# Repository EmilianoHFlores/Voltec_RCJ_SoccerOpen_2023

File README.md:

# Voltec_RCJ_SoccerOpen_2023
 Source programs. libraries, electronic schematicsm designs and CAD files from the 2023 Voltec Robocup team, participating in TMR 2023 Soccer Open category.

## Arduino Programs
 All arduino libraries and programs are created for running on an ATMEGA-2560 chip. For pin assignments, refer to the pcb schematics and design.

## PCBs
 PCB design files were created on Autodesk Eagle 9.6.2. Library requirements and references are included on folder.

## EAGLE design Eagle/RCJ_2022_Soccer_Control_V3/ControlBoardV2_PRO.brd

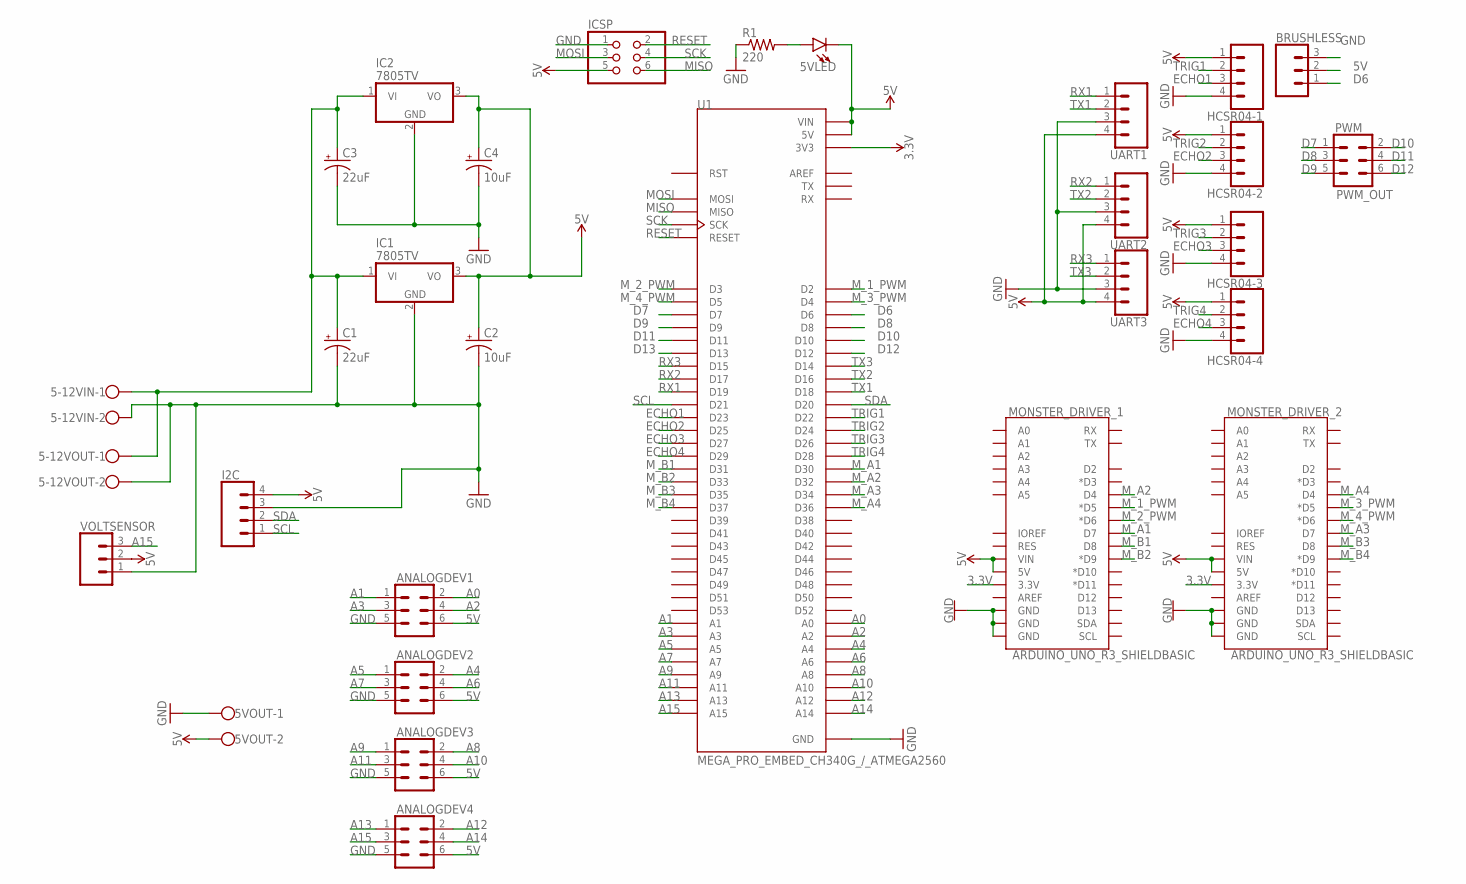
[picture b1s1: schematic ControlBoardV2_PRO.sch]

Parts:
5-12VIN, 5-12VOUT, 5VOUT: W237-102
5VLED: LED5MM; LED_5MM
ANALOGDEV1, ANALOGDEV2, ANALOGDEV3, ANALOGDEV4: CONN_03X2NO_SILK; 2X3-NS
BRUSHLESS: CONN_03; 1X03
C1, C3: 22uF; E2,5-5
C2, C4: 10uF; E2,5-5
HCSR04-1, HCSR04-2, HCSR04-3, HCSR04-4: CONN_04; 1X04
I2C: CONN_04; 1X04
IC1, IC2: 7805TV; TO220V
ICSP: PINHD-2X3; 2X03
MONSTER_DRIVER_1, MONSTER_DRIVER_2: ARDUINO_UNO_R3_SHIELDBASIC; UNO_R3_SHIELD
PWM: PWM_OUT; 2X3
R1: 220; 0204/7
U1: MEGA_PRO_EMBED_CH340G_/_ATMEGA2560; MODULE_MEGA_PRO_EMBED_CH340G_/_ATMEGA2560
UART1, UART2, UART3: CONN_04; 1X04
VOLTSENSOR: CONN_03; 1X03

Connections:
3.3V: MONSTER_DRIVER_1.3.3V, MONSTER_DRIVER_2.3.3V, U1.3V3_1 (3V3), U1.3V3_2 (3V3)
5V: 5VLED.K (C), 5VOUT.2, ANALOGDEV1.6, ANALOGDEV2.6, ANALOGDEV3.6, ANALOGDEV4.6, BRUSHLESS.2, C2.+, C4.+, HCSR04-1.1, HCSR04-2.1, HCSR04-3.1, HCSR04-4.1, I2C.4, IC1.3 (VO), IC2.3 (VO), ICSP.5, MONSTER_DRIVER_1.5V, MONSTER_DRIVER_1.VIN, MONSTER_DRIVER_2.5V, MONSTER_DRIVER_2.VIN, U1.5V_1 (5V), U1.5V_2 (5V), U1.5V_3 (5V), U1.VIN_1 (VIN), U1.VIN_2 (VIN), UART1.4, UART2.4, UART3.4, VOLTSENSOR.2
A0: ANALOGDEV1.2, U1.A0
A1: ANALOGDEV1.1, U1.A1
A2: ANALOGDEV1.4, U1.A2
A3: ANALOGDEV1.3, U1.A3
A4: ANALOGDEV2.2, U1.A4
A5: ANALOGDEV2.1, U1.A5
A6: ANALOGDEV2.4, U1.A6
A7: ANALOGDEV2.3, U1.A7
A8: ANALOGDEV3.2, U1.A8
A9: ANALOGDEV3.1, U1.A9
A10: ANALOGDEV3.4, U1.A10
A11: ANALOGDEV3.3, U1.A11
A12: ANALOGDEV4.2, U1.A12
A13: ANALOGDEV4.1, U1.A13
A14: ANALOGDEV4.4, U1.A14
A15: ANALOGDEV4.3, U1.A15, VOLTSENSOR.3
D6: BRUSHLESS.1, U1.D6
D7: PWM.1, U1.D7
D8: PWM.3, U1.D8
D9: PWM.5, U1.D9
D10: PWM.2, U1.D10
D11: PWM.4, U1.D11
D12: PWM.6, U1.D12
D13: U1.D13
ECHO1: HCSR04-1.3, U1.D23
ECHO2: HCSR04-2.3, U1.D25
ECHO3: HCSR04-3.3, U1.D27
ECHO4: HCSR04-4.3, U1.D29
GND: 5-12VIN.2, 5-12VOUT.2, 5VOUT.1, ANALOGDEV1.5, ANALOGDEV2.5, ANALOGDEV3.5, ANALOGDEV4.5, BRUSHLESS.3, C1.-, C2.-, C3.-, C4.-, HCSR04-1.4, HCSR04-2.4, HCSR04-3.4, HCSR04-4.4, I2C.3, IC1.2 (GND), IC2.2 (GND), ICSP.1, MONSTER_DRIVER_1.GND@0 (GND), MONSTER_DRIVER_1.GND@1 (GND), MONSTER_DRIVER_1.GND@2 (GND), MONSTER_DRIVER_2.GND@0 (GND), MONSTER_DRIVER_2.GND@1 (GND), MONSTER_DRIVER_2.GND@2 (GND), R1.1, U1.GND_1 (GND), U1.GND_2 (GND), U1.GND_3 (GND), UART1.3, UART2.3, UART3.3, VOLTSENSOR.1
MISO: ICSP.6, U1.MISO
MOSI: ICSP.3, U1.MOSI
M_1_PWM: MONSTER_DRIVER_1.D5 (*D5), U1.D2
M_2_PWM: MONSTER_DRIVER_1.D6 (*D6), U1.D3
M_3_PWM: MONSTER_DRIVER_2.D5 (*D5), U1.D4
M_4_PWM: MONSTER_DRIVER_2.D6 (*D6), U1.D5
M_A1: MONSTER_DRIVER_1.D7, U1.D30
M_A2: MONSTER_DRIVER_1.D4, U1.D32
M_A3: MONSTER_DRIVER_2.D7, U1.D34
M_A4: MONSTER_DRIVER_2.D4, U1.D36
M_B1: MONSTER_DRIVER_1.D8, U1.D31
M_B2: MONSTER_DRIVER_1.D9 (*D9), U1.D33
M_B3: MONSTER_DRIVER_2.D8, U1.D35
M_B4: MONSTER_DRIVER_2.D9 (*D9), U1.D37
unnamed: 5VLED.A, R1.2
unnamed: 5-12VIN.1, 5-12VOUT.1, C1.+, C3.+, IC1.1 (VI), IC2.1 (VI)
RESET: ICSP.2, U1.RESET
RX1: U1.D19, UART1.1
RX2: U1.D17, UART2.1
RX3: U1.D15, UART3.1
SCK: ICSP.4, U1.SCK
SCL: I2C.1, U1.D21
SDA: I2C.2, U1.D20
TRIG1: HCSR04-1.2, U1.D22
TRIG2: HCSR04-2.2, U1.D24
TRIG3: HCSR04-3.2, U1.D26
TRIG4: HCSR04-4.2, U1.D28
TX1: U1.D18, UART1.2
TX2: U1.D16, UART2.2
TX3: U1.D14, UART3.2

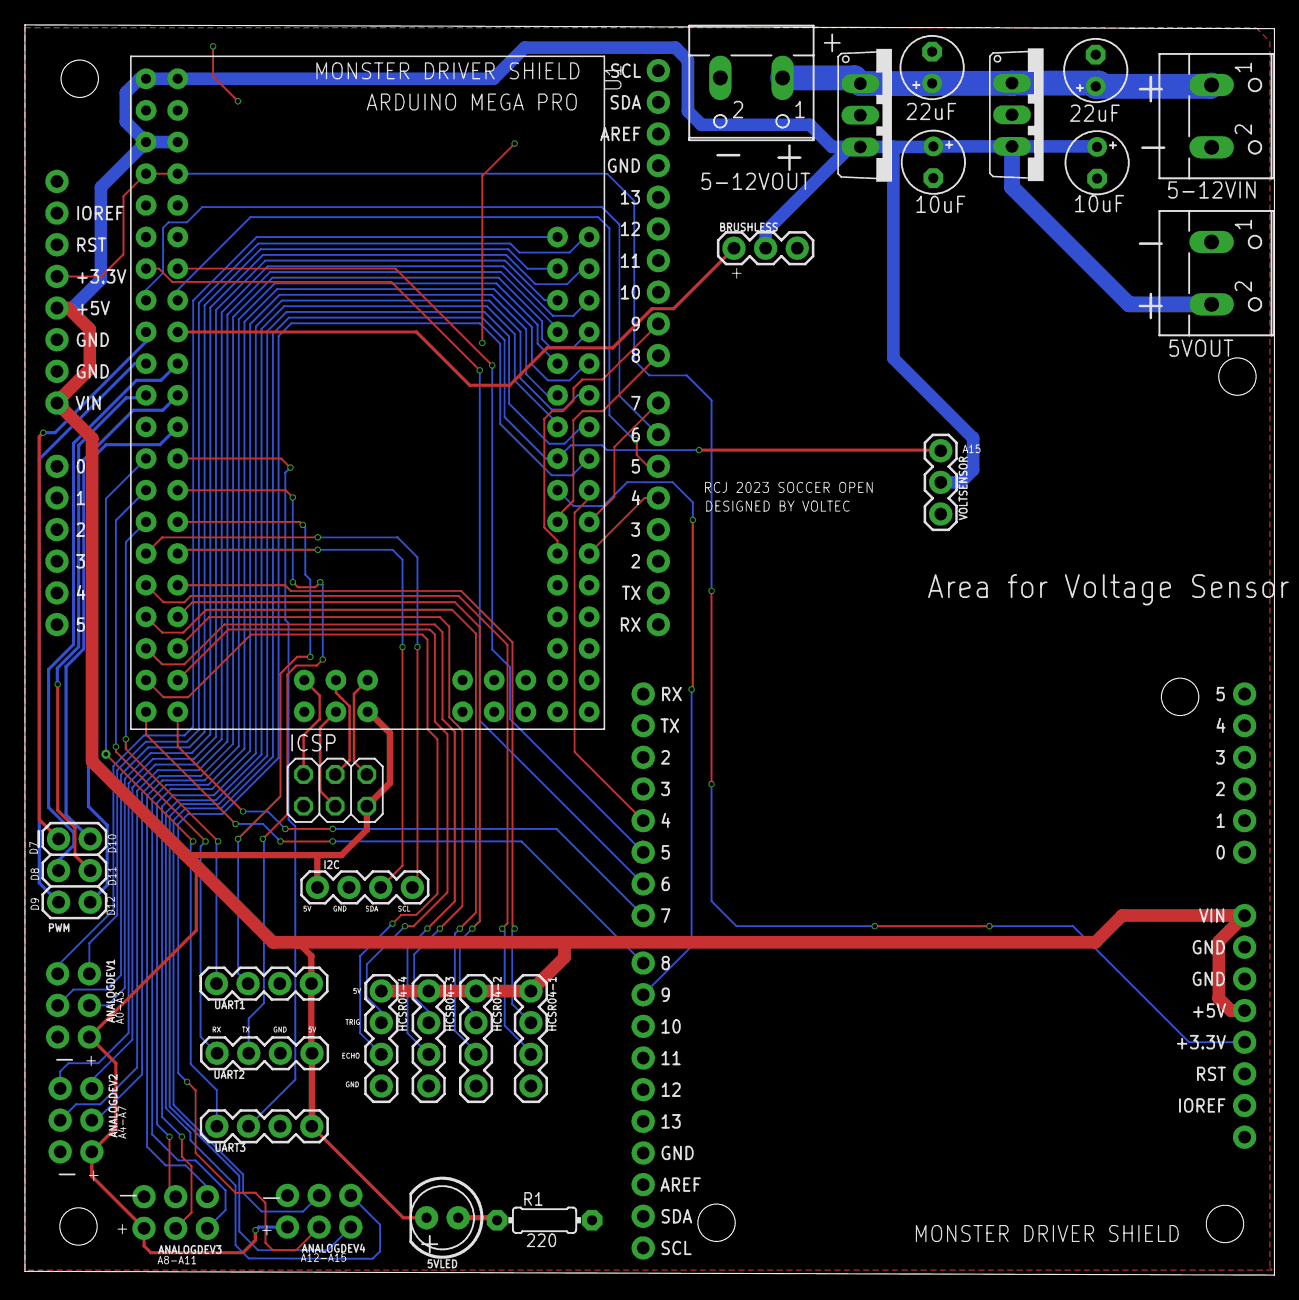
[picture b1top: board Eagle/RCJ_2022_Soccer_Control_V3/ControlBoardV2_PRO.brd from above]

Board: 2 copper layers, 100.3 x 100.3 mm, 30 parts (0 on the bottom side), 60 nets.

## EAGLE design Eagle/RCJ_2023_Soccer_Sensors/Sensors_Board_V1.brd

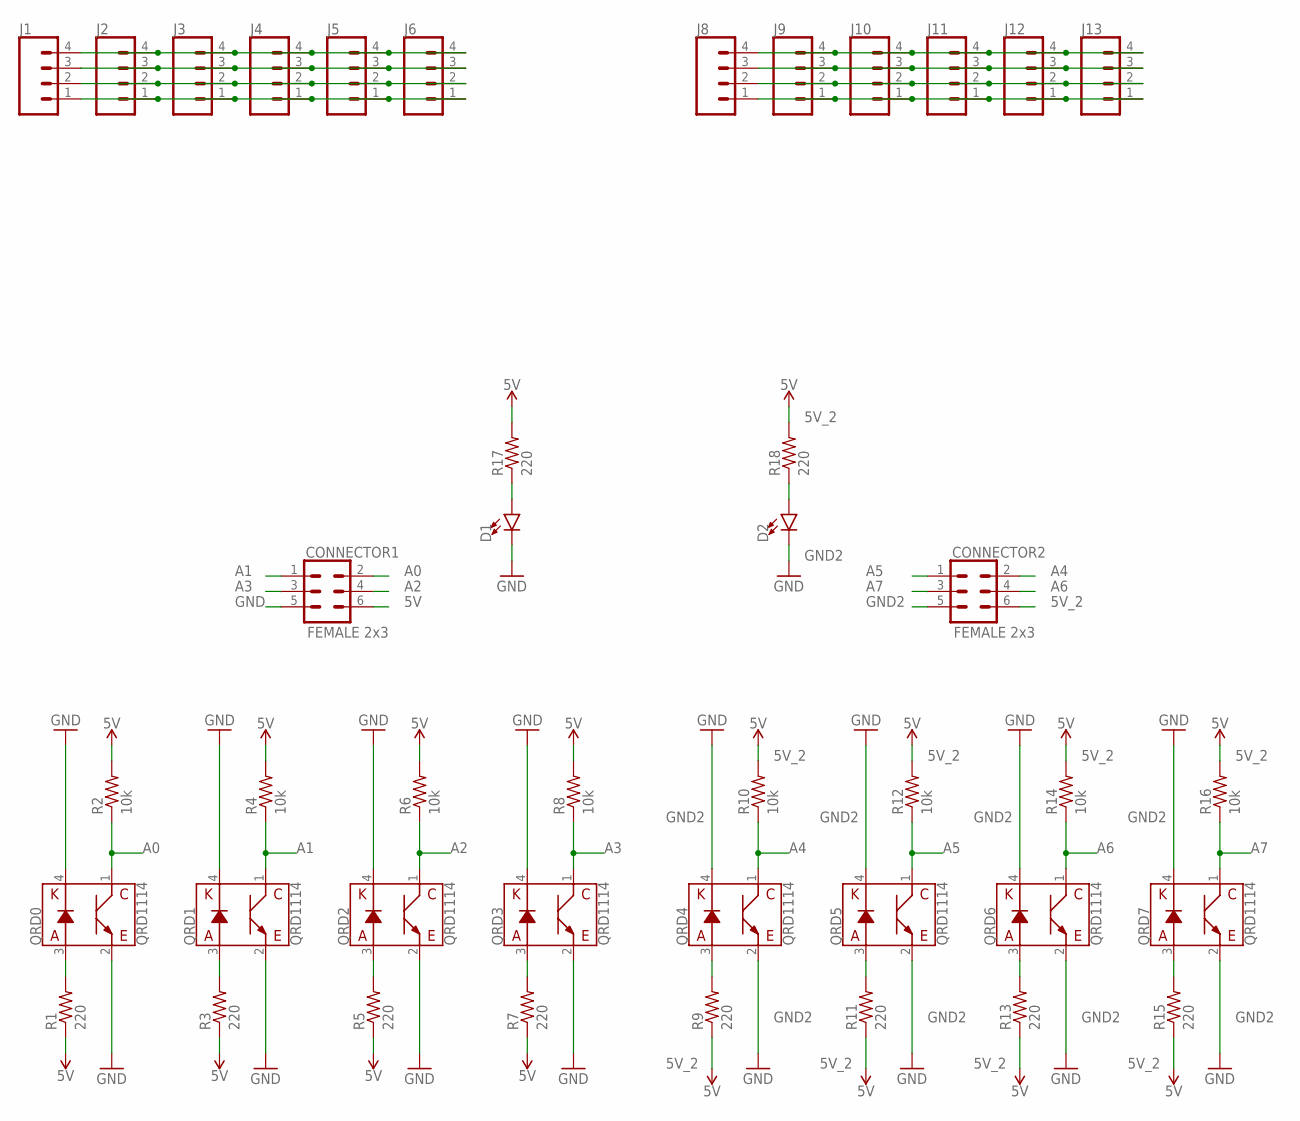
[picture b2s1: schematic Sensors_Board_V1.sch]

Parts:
CONNECTOR1, CONNECTOR2: FEMALE 2x3; 2X3
D1, D2: LED3MM; LED_3MM
J1, J2, J3, J4, J5, J6, J8, J9, J10, J11, J12, J13: CONN_04; 1X04
QRD0, QRD1, QRD2, QRD3, QRD4, QRD5, QRD6, QRD7: QRD1114
R1, R3, R5, R7, R9, R11, R13, R15, R17, R18: 220; 0204/7
R2, R4, R6, R8, R10, R12, R14, R16: 10k; 0204/7

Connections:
5V: CONNECTOR1.6, R1.1, R2.2, R3.1, R4.2, R5.1, R6.2, R7.1, R8.2, R17.2
5V_2: CONNECTOR2.6, R9.1, R10.2, R11.1, R12.2, R13.1, R14.2, R15.1, R16.2, R18.2
A0: CONNECTOR1.2, QRD0.1 (C), R2.1
A1: CONNECTOR1.1, QRD1.1 (C), R4.1
A2: CONNECTOR1.4, QRD2.1 (C), R6.1
A3: CONNECTOR1.3, QRD3.1 (C), R8.1
A4: CONNECTOR2.2, QRD4.1 (C), R10.1
A5: CONNECTOR2.1, QRD5.1 (C), R12.1
A6: CONNECTOR2.4, QRD6.1 (C), R14.1
A7: CONNECTOR2.3, QRD7.1 (C), R16.1
GND: CONNECTOR1.5, D1.K (C), QRD0.2 (E), QRD0.4 (K), QRD1.2 (E), QRD1.4 (K), QRD2.2 (E), QRD2.4 (K), QRD3.2 (E), QRD3.4 (K)
GND2: CONNECTOR2.5, D2.K (C), QRD4.2 (E), QRD4.4 (K), QRD5.2 (E), QRD5.4 (K), QRD6.2 (E), QRD6.4 (K), QRD7.2 (E), QRD7.4 (K)
unnamed: QRD0.3 (A), R1.2
unnamed: QRD1.3 (A), R3.2
unnamed: QRD2.3 (A), R5.2
unnamed: QRD3.3 (A), R7.2
unnamed: QRD4.3 (A), R9.2
unnamed: QRD5.3 (A), R11.2
unnamed: QRD6.3 (A), R13.2
unnamed: QRD7.3 (A), R15.2
unnamed: D1.A, R17.1
unnamed: D2.A, R18.1
unnamed: J1.4, J2.4, J3.4, J4.4, J5.4, J6.4
unnamed: J1.3, J2.3, J3.3, J4.3, J5.3, J6.3
unnamed: J1.2, J2.2, J3.2, J4.2, J5.2, J6.2
unnamed: J1.1, J2.1, J3.1, J4.1, J5.1, J6.1
unnamed: J8.4, J9.4, J10.4, J11.4, J12.4, J13.4
unnamed: J8.3, J9.3, J10.3, J11.3, J12.3, J13.3
unnamed: J8.2, J9.2, J10.2, J11.2, J12.2, J13.2
unnamed: J8.1, J9.1, J10.1, J11.1, J12.1, J13.1

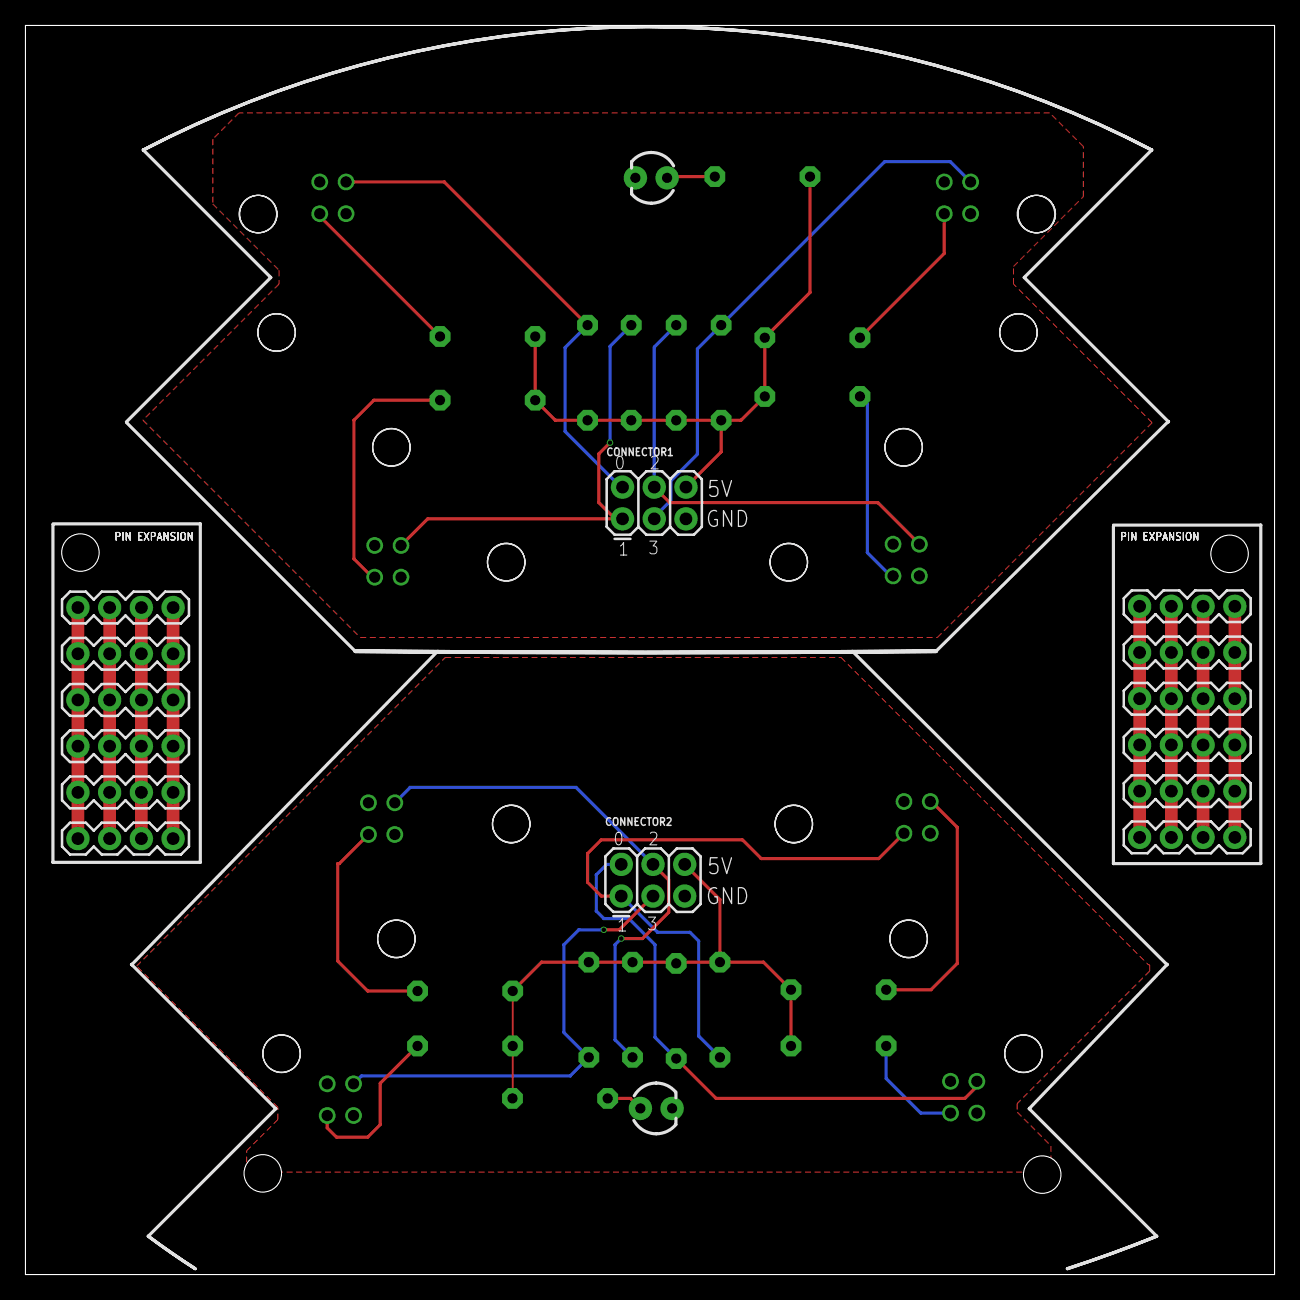
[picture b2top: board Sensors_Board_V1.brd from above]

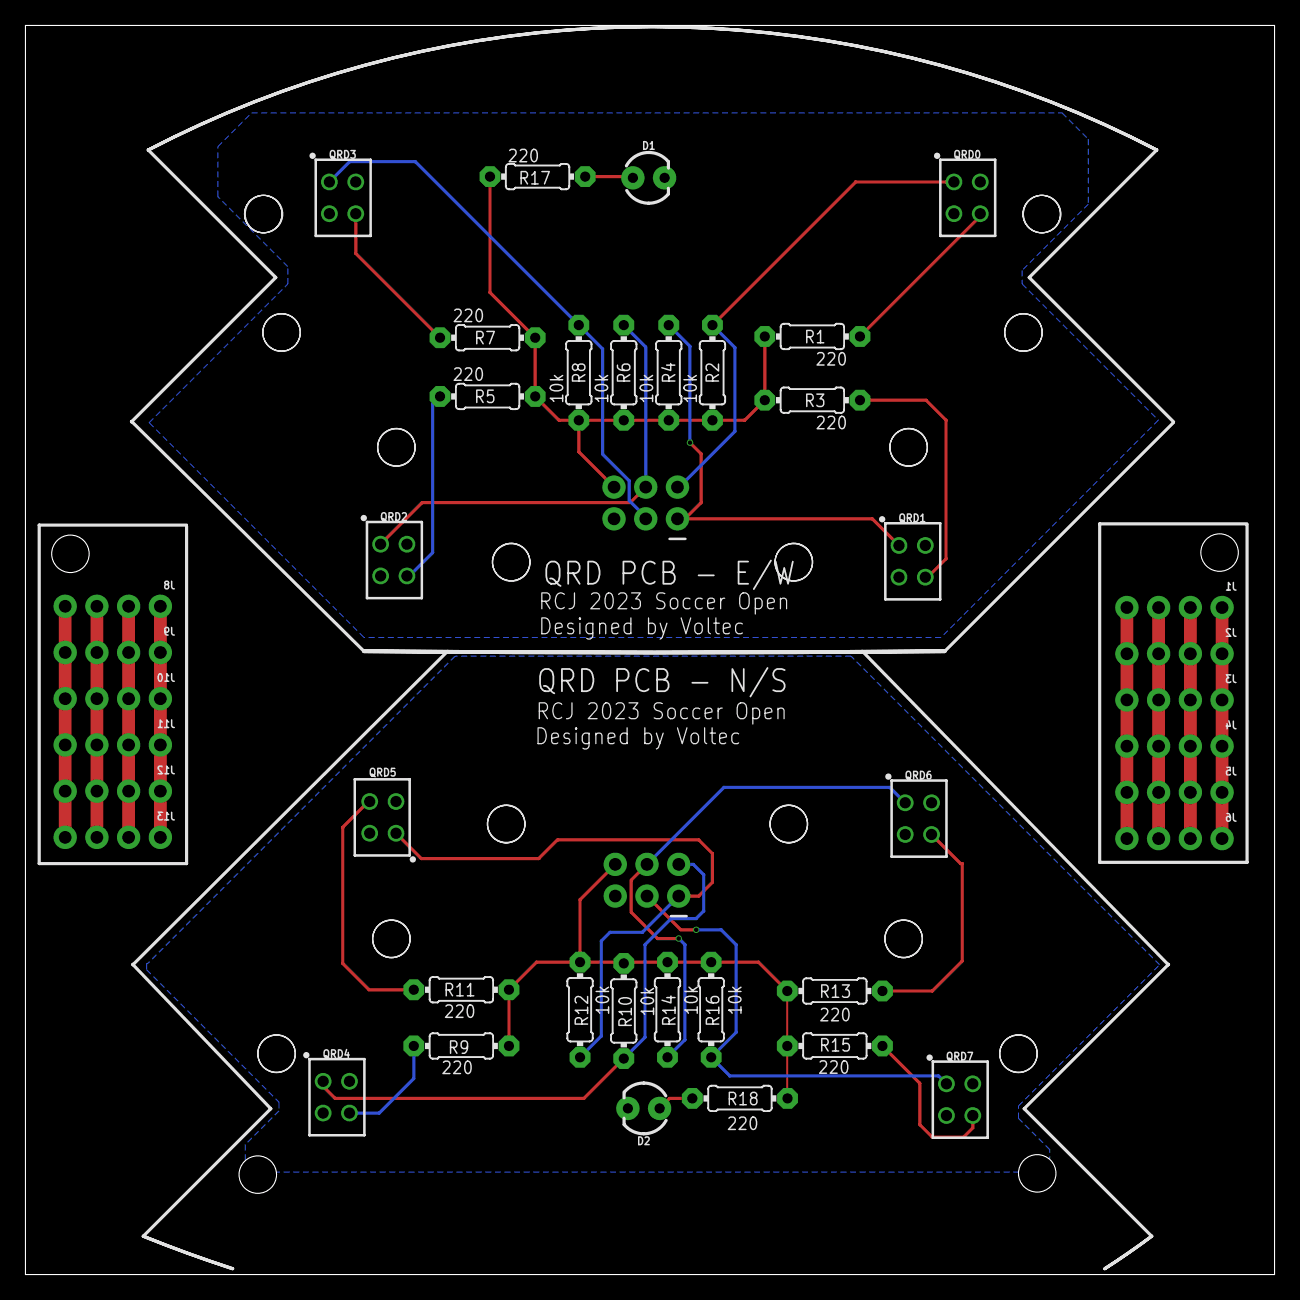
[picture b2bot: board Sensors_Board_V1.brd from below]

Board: 2 copper layers, 100.0 x 100.0 mm, 42 parts (28 on the bottom side), 30 nets.

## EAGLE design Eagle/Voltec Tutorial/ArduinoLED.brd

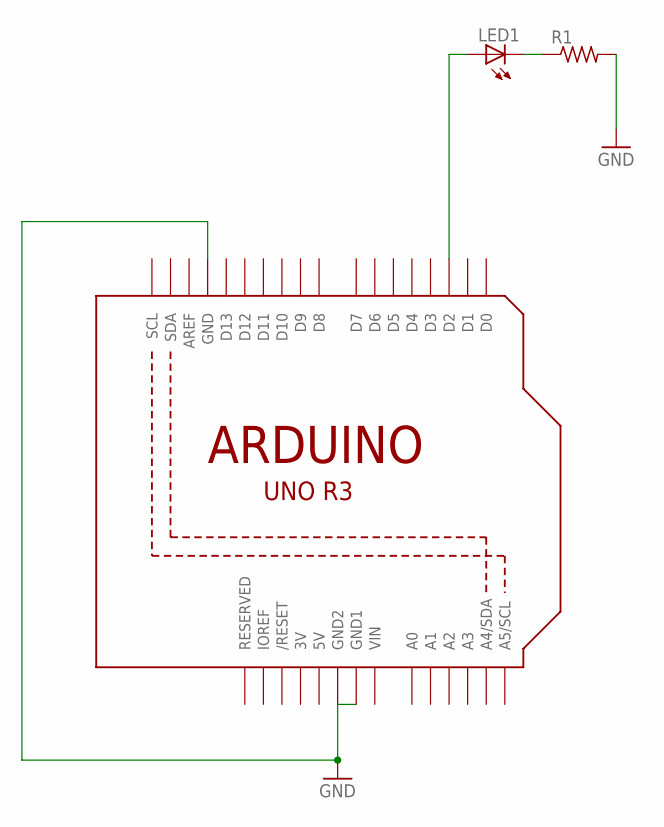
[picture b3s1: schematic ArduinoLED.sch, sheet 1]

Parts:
LED1: LED5MM
R1: R-US_0204/7; 0204/7
U1: ARDUINOR3-BPLACE

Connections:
3V: U1.3V
5V: U1.5V
GND: R1.2, U1.GND, U1.GND1, U1.GND2
unnamed: LED1.A, U1.D2
unnamed: LED1.K (C), R1.1
VIN: U1.VIN

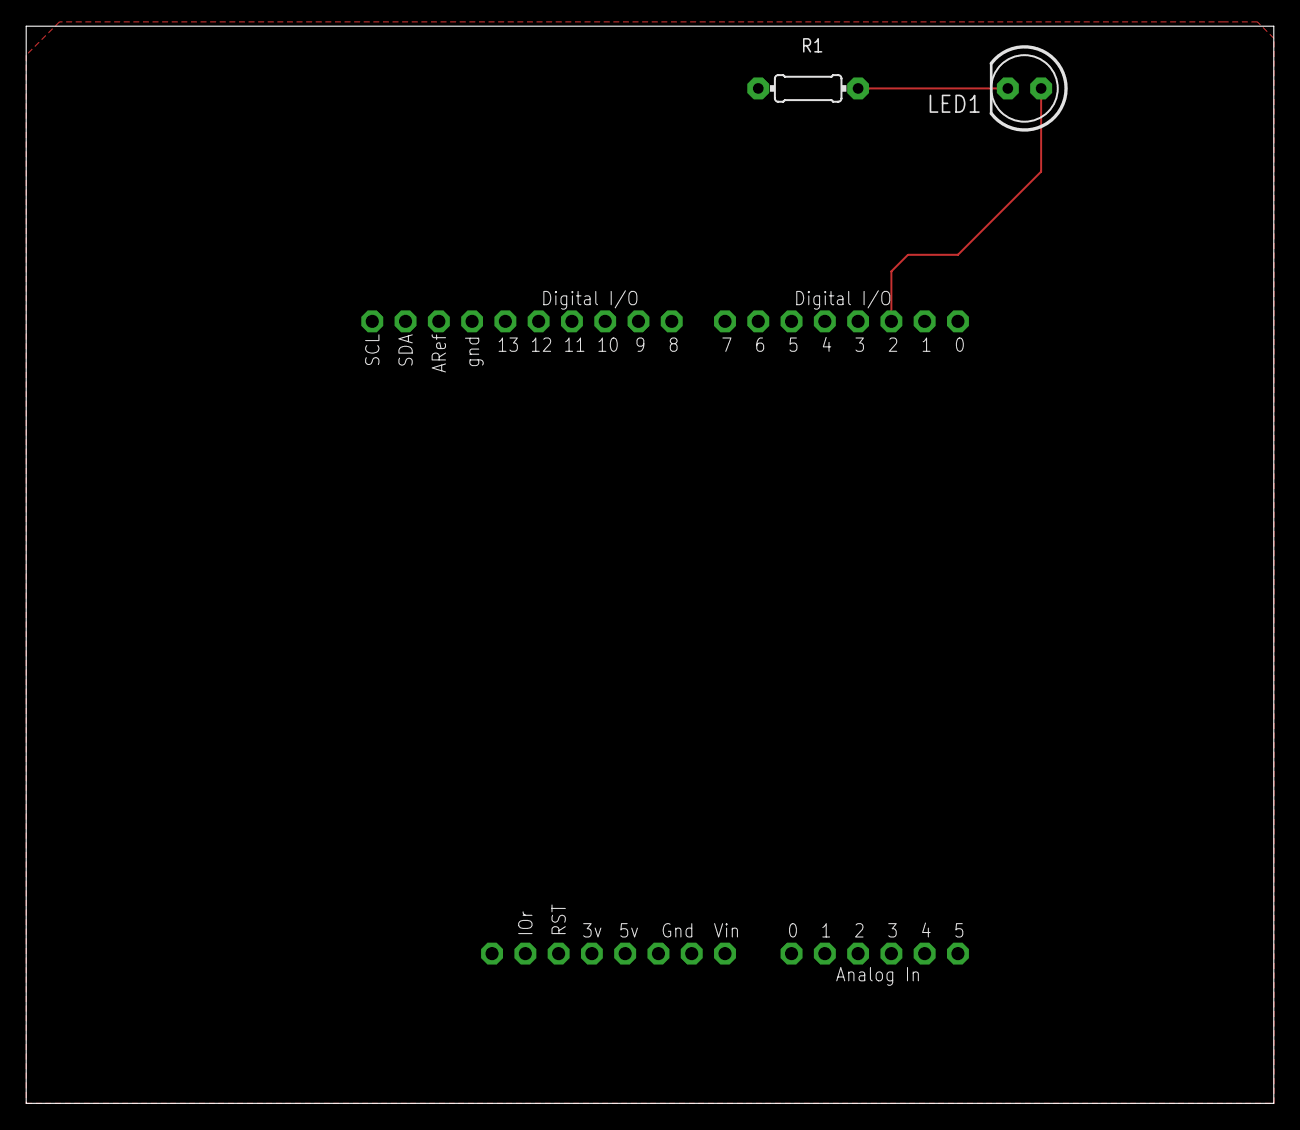
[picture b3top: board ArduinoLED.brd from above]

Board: 2 copper layers, 95.2 x 82.2 mm, 3 parts (0 on the bottom side), 3 nets.

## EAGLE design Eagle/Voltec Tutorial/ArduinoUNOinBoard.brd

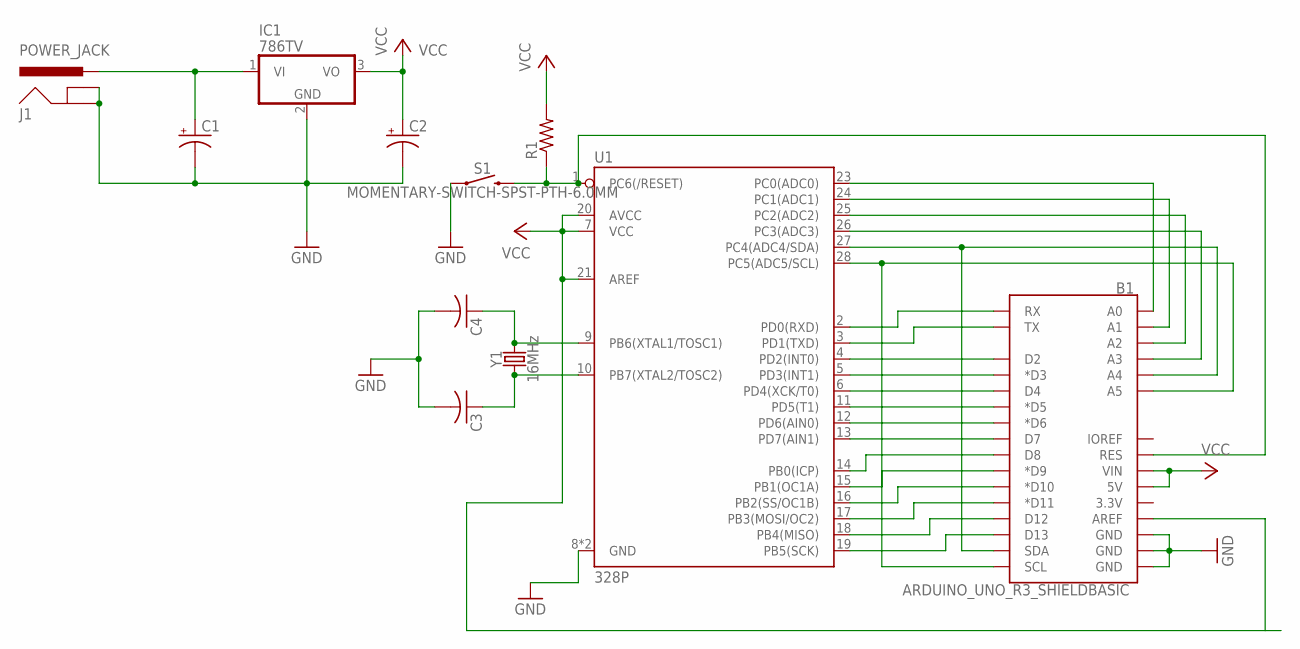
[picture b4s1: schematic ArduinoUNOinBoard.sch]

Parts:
B1: ARDUINO_UNO_R3_SHIELDBASIC; UNO_R3_SHIELD
C1, C2: CPOL-USE2,5-6E; E2,5-6E
C3, C4: C-US025-024X044; C025-024X044
IC1: 786TV; TO220V
J1: POWER_JACK; POWER_JACK_PTH
R1: R-US_0204/7; 0204/7
S1: MOMENTARY-SWITCH-SPST-PTH-6.0MM; TACTILE_SWITCH_PTH_6.0MM
U1: 328P; DIP28
Y1: 16MHz; HC49US

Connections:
GND: B1.GND@0 (GND), B1.GND@1 (GND), B1.GND@2 (GND), C1.-, C2.-, C3.2, C4.2, IC1.2 (GND), J1.GND, J1.GNDBREAK, S1.1, U1.8 (GND), U1.22 (GND)
unnamed: C1.+, IC1.1 (VI), J1.PWR
unnamed: C4.1, U1.9 (PB6(XTAL1/TOSC1)), Y1.2
unnamed: C3.1, U1.10 (PB7(XTAL2/TOSC2)), Y1.1
unnamed: B1.RES, R1.1, S1.3 (2), U1.1 (PC6(/RESET))
unnamed: B1.RX, U1.2 (PD0(RXD))
unnamed: B1.TX, U1.3 (PD1(TXD))
unnamed: B1.D2, U1.4 (PD2(INT0))
unnamed: B1.D3 (*D3), U1.5 (PD3(INT1))
unnamed: B1.D4, U1.6 (PD4(XCK/T0))
unnamed: B1.D5 (*D5), U1.11 (PD5(T1))
unnamed: B1.D6 (*D6), U1.12 (PD6(AIN0))
unnamed: B1.D7, U1.13 (PD7(AIN1))
unnamed: B1.D8, U1.14 (PB0(ICP))
unnamed: B1.D9 (*D9), U1.15 (PB1(OC1A))
unnamed: B1.D10 (*D10), U1.16 (PB2(SS/OC1B))
unnamed: B1.D11 (*D11), U1.17 (PB3(MOSI/OC2))
unnamed: B1.D12, U1.18 (PB4(MISO))
unnamed: B1.D13, U1.19 (PB5(SCK))
unnamed: B1.A0, U1.23 (PC0(ADC0))
unnamed: B1.A1, U1.24 (PC1(ADC1))
unnamed: B1.A2, U1.25 (PC2(ADC2))
unnamed: B1.A3, U1.26 (PC3(ADC3))
unnamed: B1.A4, B1.SDA, U1.27 (PC4(ADC4/SDA))
unnamed: B1.A5, B1.SCL, U1.28 (PC5(ADC5/SCL))
VCC: B1.5V, B1.AREF, B1.VIN, C2.+, IC1.3 (VO), R1.2, U1.7 (VCC), U1.20 (AVCC), U1.21 (AREF)

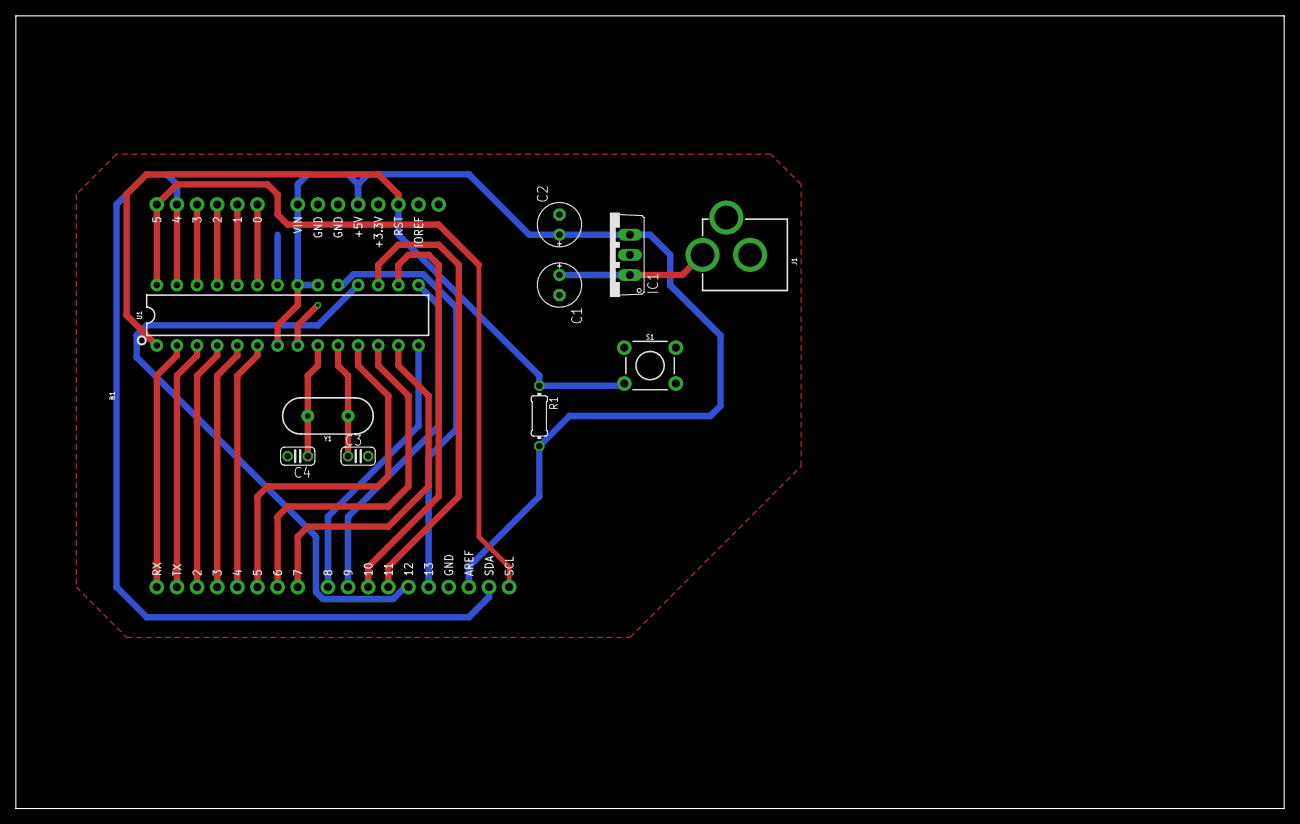
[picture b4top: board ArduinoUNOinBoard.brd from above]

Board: 2 copper layers, 160.0 x 100.0 mm, 11 parts (0 on the bottom side), 26 nets.

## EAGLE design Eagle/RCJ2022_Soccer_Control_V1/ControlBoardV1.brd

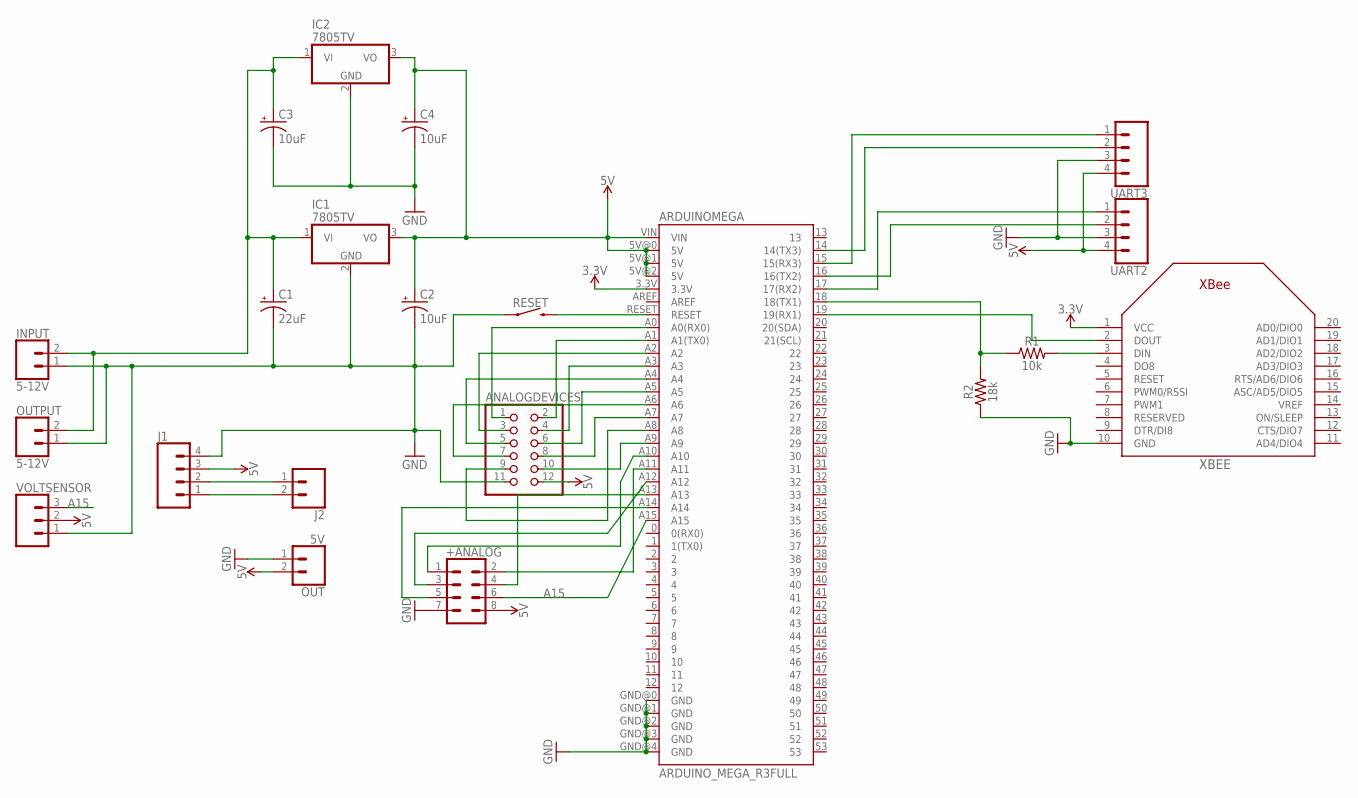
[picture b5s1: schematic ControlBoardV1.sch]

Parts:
+ANALOG: CONN_04X2; 2X4
ANALOGDEVICES: PINHD-2X6; 2X06
ARDUINOMEGA: ARDUINO_MEGA_R3FULL; ARDUINO_MEGA
C1: 22uF; E2,5-5
C2, C3, C4: 10uF; E2,5-5
IC1, IC2: 7805TV; TO220V
INPUT: 5-12V; SCREWTERMINAL-3.5MM-2
J1: CONN_04; 1X04
J2: CONN_02; 1X02
OUT: 5V; SCREWTERMINAL-3.5MM-2
OUTPUT: 5-12V; SCREWTERMINAL-3.5MM-2
R1: 10k; AXIAL-0.3
R2: 18k; AXIAL-0.3
RESET: MOMENTARY-SWITCH-SPST-PTH-6.0MM; TACTILE_SWITCH_PTH_6.0MM
UART2, UART3: CONN_04; 1X04
VOLTSENSOR: CONN_03; 1X03
XBEE: XBEE

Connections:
3.3V: ARDUINOMEGA.3.3V, XBEE.1 (VCC)
5V: +ANALOG.8, ANALOGDEVICES.12, ARDUINOMEGA.5V@0 (5V), ARDUINOMEGA.5V@1 (5V), ARDUINOMEGA.5V@2 (5V), ARDUINOMEGA.VIN, C2.+, C4.+, IC1.3 (VO), IC2.3 (VO), J1.3, OUT.2, UART2.4, UART3.4, VOLTSENSOR.2
A15: +ANALOG.6, ARDUINOMEGA.A15, VOLTSENSOR.3
GND: +ANALOG.7, ANALOGDEVICES.11, ARDUINOMEGA.GND@0 (GND), ARDUINOMEGA.GND@1 (GND), ARDUINOMEGA.GND@2 (GND), ARDUINOMEGA.GND@3 (GND), ARDUINOMEGA.GND@4 (GND), C1.-, C2.-, C3.-, C4.-, IC1.2 (GND), IC2.2 (GND), INPUT.1, J1.4, OUT.1, OUTPUT.1, R2.P$1 (1), RESET.1, UART2.3, UART3.3, VOLTSENSOR.1, XBEE.10 (GND)
unnamed: ANALOGDEVICES.1, ARDUINOMEGA.A0 (A0(RX0))
unnamed: ARDUINOMEGA.19 (19(RX1)), XBEE.2 (DOUT)
unnamed: ARDUINOMEGA.15 (15(RX3)), UART3.1
unnamed: ARDUINOMEGA.14 (14(TX3)), UART3.2
unnamed: ARDUINOMEGA.17 (17(RX2)), UART2.1
unnamed: ARDUINOMEGA.16 (16(TX2)), UART2.2
unnamed: ARDUINOMEGA.18 (18(TX1)), R1.P$1 (1), R2.P$2 (2)
unnamed: ANALOGDEVICES.2, ARDUINOMEGA.A1 (A1(TX0))
unnamed: R1.P$2 (2), XBEE.3 (DIN)
unnamed: ARDUINOMEGA.RESET, RESET.3 (2)
unnamed: C1.+, C3.+, IC1.1 (VI), IC2.1 (VI), INPUT.2, OUTPUT.2
unnamed: ANALOGDEVICES.3, ARDUINOMEGA.A2
unnamed: ANALOGDEVICES.5, ARDUINOMEGA.A4
unnamed: ANALOGDEVICES.7, ARDUINOMEGA.A6
unnamed: ANALOGDEVICES.4, ARDUINOMEGA.A3
unnamed: ANALOGDEVICES.6, ARDUINOMEGA.A5
unnamed: ANALOGDEVICES.8, ARDUINOMEGA.A7
unnamed: ANALOGDEVICES.9, ARDUINOMEGA.A8
unnamed: ANALOGDEVICES.10, ARDUINOMEGA.A9
unnamed: J1.1, J2.2
unnamed: J1.2, J2.1
unnamed: +ANALOG.2, ARDUINOMEGA.A11
unnamed: +ANALOG.1, ARDUINOMEGA.A10
unnamed: +ANALOG.3, ARDUINOMEGA.A12
unnamed: +ANALOG.4, ARDUINOMEGA.A13
unnamed: +ANALOG.5, ARDUINOMEGA.A14

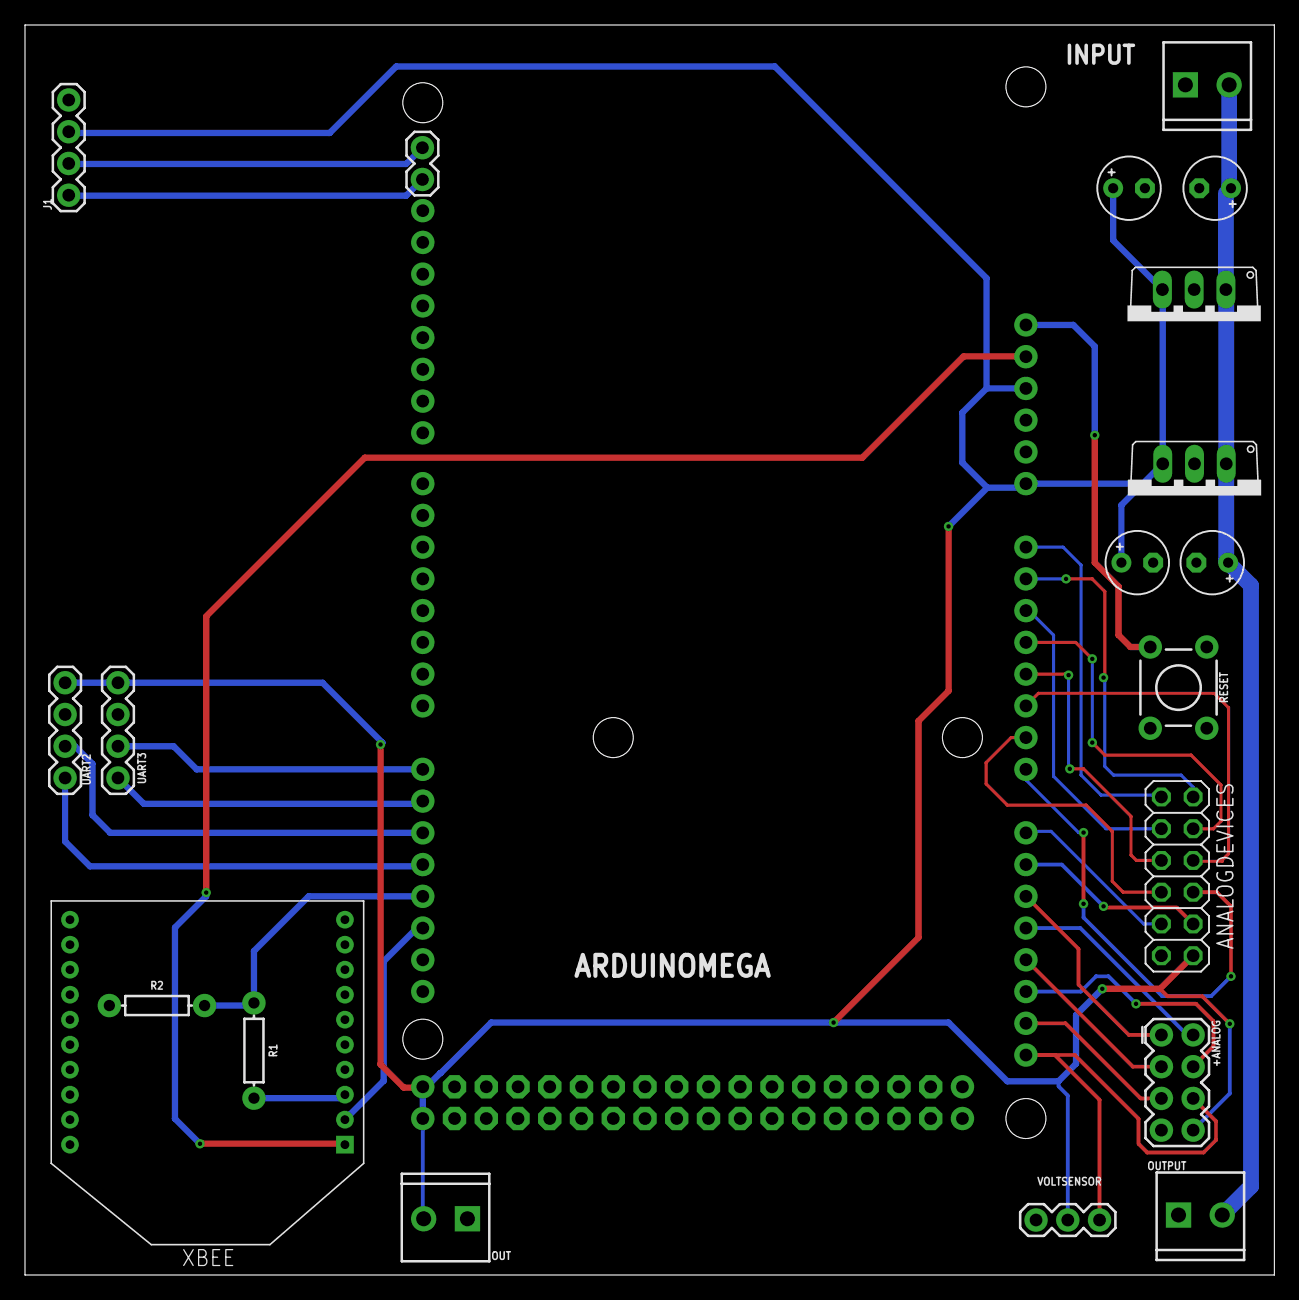
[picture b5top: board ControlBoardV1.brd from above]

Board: 2 copper layers, 100.0 x 100.0 mm, 21 parts (1 on the bottom side), 30 nets.

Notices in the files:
parts and their libraries:
SparkFun-Boards: Licensing: Creative Commons ShareAlike 4.0 International - https://creativecommons.org/licenses/by-sa/4.0
